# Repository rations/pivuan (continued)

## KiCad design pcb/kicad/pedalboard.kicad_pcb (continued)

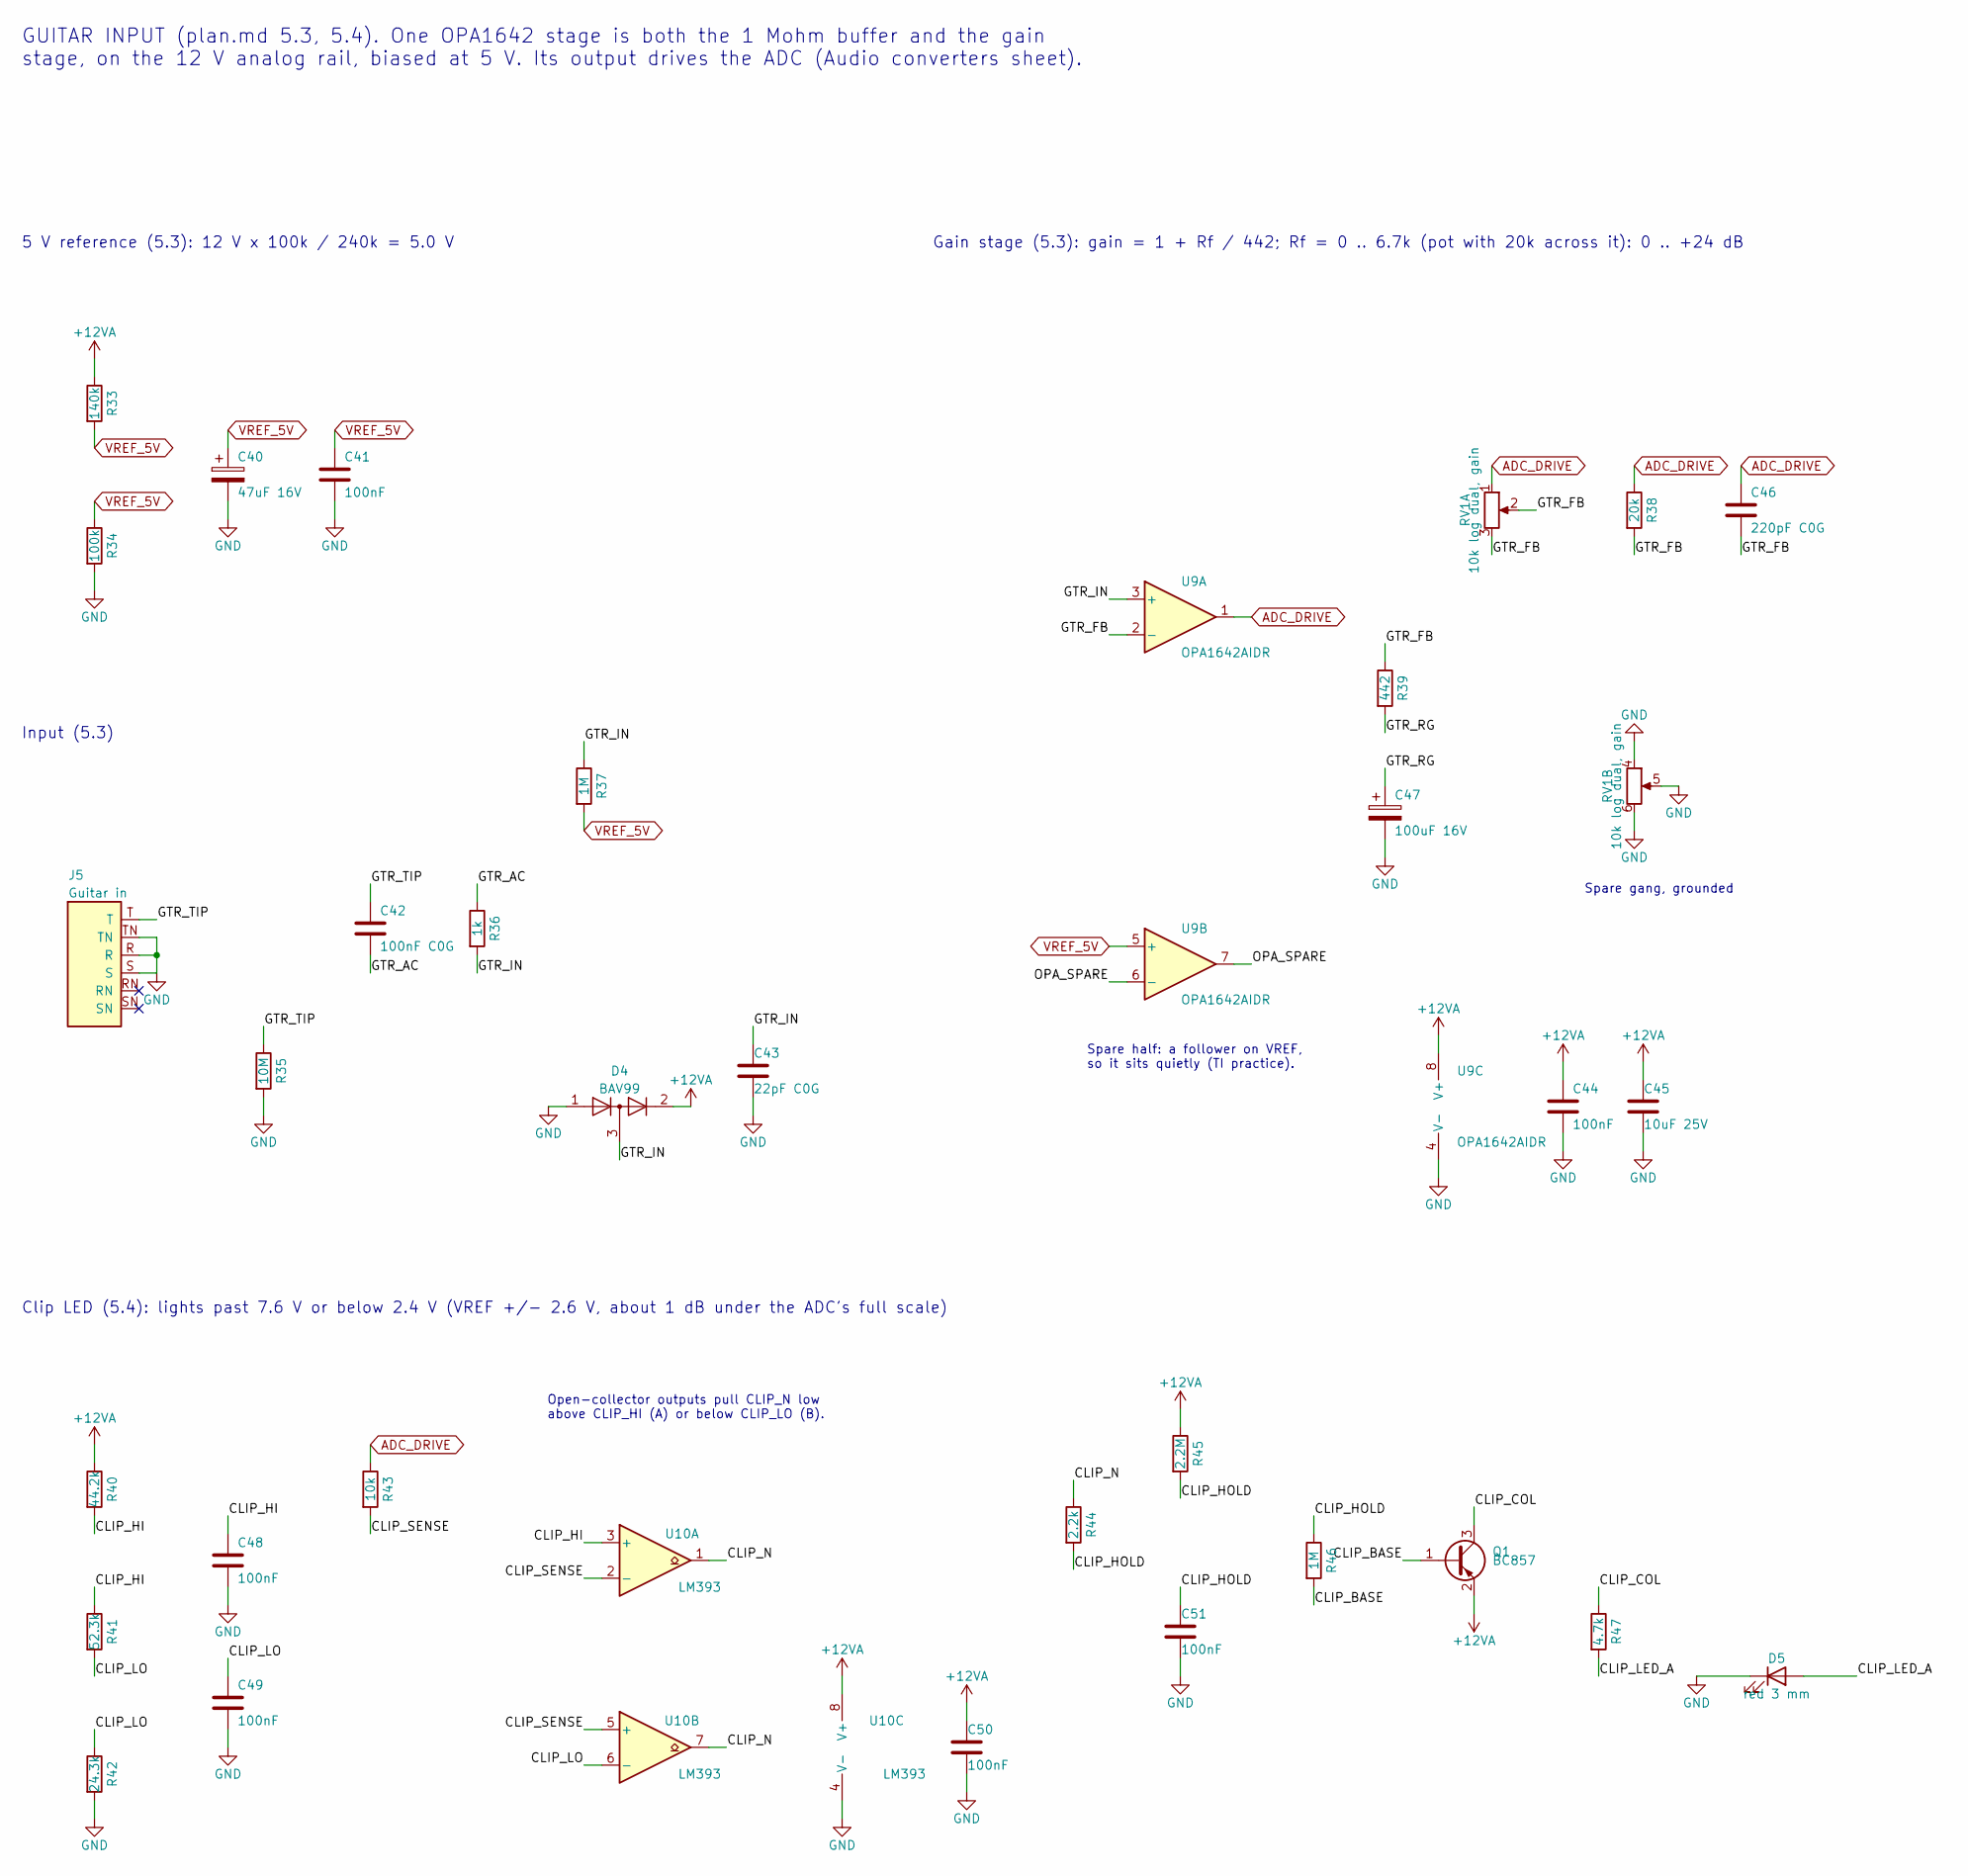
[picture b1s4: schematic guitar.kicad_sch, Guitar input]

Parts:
C40: 47uF 16V; CP_Elec_5x5.4; MPN RVT1C470M0505; LCSC C72515
C41, C44, C48, C49, C50, C51: 100nF; C_0603_1608Metric; MPN CC0603KRX7R9BB104; LCSC C14663
C42: 100nF C0G; C_1206_3216Metric; MPN GRM31C5C1H104JA01L; LCSC C97946
C43: 22pF C0G; C_0603_1608Metric; MPN CL10C220JB8NNNC; LCSC C1653
C45: 10uF 25V; C_1206_3216Metric; MPN CL31A106KBHNNNE; LCSC C13585
C46: 220pF C0G; C_0603_1608Metric; MPN GCM1885C2A221JA16D; LCSC C388907
C47: 100uF 16V; CP_Elec_6.3x5.4; MPN RVT1C101M0605; LCSC C72475
D4: BAV99; SOT-23; MPN BAV99,215; LCSC C2500
D5: red 3 mm; LED_D3.0mm_Horizontal_O1.27mm_Z6.0mm; MPN 204-10SURD/S530-A3-L; LCSC C99771
J5: Guitar in; Jack_6.35mm_Neutrik_NMJ6HCD2_Horizontal; MPN NMJ6HCD2; LCSC C368502
Q1: BC857; SOT-23; MPN BC857C,215; LCSC C8666
R33: 140k; R_0603_1608Metric; MPN RC0603FR-07140KL; LCSC C185372
R34: 100k; R_0603_1608Metric; MPN 0603WAF1003T5E; LCSC C25803
R35: 10M; R_0603_1608Metric; MPN 0603WAF1005T5E; LCSC C7250
R36: 1k; R_0603_1608Metric; MPN 0603WAF1001T5E; LCSC C21190
R37, R46: 1M; R_0603_1608Metric; MPN 0603WAF1004T5E; LCSC C22935
R38: 20k; R_0603_1608Metric; MPN 0603WAF2002T5E; LCSC C4184
R39: 442; R_0603_1608Metric; MPN 0603WAF4420T5E; LCSC C23057
R40: 44.2k; R_0603_1608Metric; MPN AT0603BRD0744K2L; LCSC C855860
R41: 52.3k; R_0603_1608Metric; MPN RS-03K5232FT; LCSC C304764
R42: 24.3k; R_0603_1608Metric; MPN RT0603BRD0724K3L; LCSC C136968
R43: 10k; R_0603_1608Metric; MPN 0603WAF1002T5E; LCSC C25804
R44: 2.2k; R_0603_1608Metric; MPN 0603WAF2201T5E; LCSC C4190
R45: 2.2M; R_0603_1608Metric; MPN 0603WAF2204T5E; LCSC C22938
R47: 4.7k; R_0603_1608Metric; MPN 0603WAF4701T5E; LCSC C23162
RV1: 10k log dual, gain; Potentiometer_Alps_RK09L_Double_Horizontal; MPN RK09L12B0A4S
U9: OPA1642AIDR; SOIC-8_3.9x4.9mm_P1.27mm; MPN OPA1642AIDR; LCSC C67640
U10: LM393; SOIC-8_3.9x4.9mm_P1.27mm; MPN LM393DR2G; LCSC C7955

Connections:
+12VA: C44.1, C45.1, C50.1, D4.2 (A), Q1.2 (E), R33.1, R40.1, R45.1, U9.8 (V+), U10.8 (V+); also elsewhere on the board
/Guitar input/CLIP_BASE: Q1.1 (B), R46.2
/Guitar input/CLIP_COL: Q1.3 (C), R47.1
/Guitar input/CLIP_HI: C48.1, R40.2, R41.1, U10.3 (+)
/Guitar input/CLIP_HOLD: C51.1, R44.2, R45.2, R46.1
/Guitar input/CLIP_LED_A: D5.2 (A), R47.2
/Guitar input/CLIP_LO: C49.1, R41.2, R42.1, U10.6 (-)
/Guitar input/CLIP_N: R44.1, U10.1, U10.7
/Guitar input/CLIP_SENSE: R43.2, U10.2 (-), U10.5 (+)
/Guitar input/GTR_AC: C42.2, R36.1
/Guitar input/GTR_FB: C46.2, R38.2, R39.1, RV1.2, RV1.3, U9.2 (-)
/Guitar input/GTR_IN: C43.1, D4.3 (K), R36.2, R37.1, U9.3 (+)
/Guitar input/GTR_RG: C47.1, R39.2
/Guitar input/GTR_TIP: C42.1, J5.T, R35.1
/Guitar input/OPA_SPARE: U9.6 (-), U9.7
ADC_DRIVE: C46.1, R38.1, R43.1, RV1.1, U9.1; also elsewhere on the board
GND: C40.2, C41.2, C43.2, C44.2, C45.2, C47.2, C48.2, C49.2, C50.2, C51.2, D4.1 (K), D5.1 (K), J5.R, J5.S, J5.TN, R34.2, R35.2, R42.2, RV1.4, RV1.5, RV1.6, U9.4 (V-), U10.4 (V-); also elsewhere on the board
VREF_5V: C40.1, C41.1, R33.2, R34.1, R37.2, U9.5 (+); also elsewhere on the board

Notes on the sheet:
GUITAR INPUT (plan.md 5.3, 5.4). One OPA1642 stage is both the 1 Mohm buffer and the gain stage, on the 12 V analog rail, biased at 5 V. Its output drives the ADC (Audio converters sheet).
5 V reference (5.3): 12 V x 100k / 240k = 5.0 V
Input (5.3)
Gain stage (5.3): gain = 1 + Rf / 442; Rf = 0 .. 6.7k (pot with 20k across it): 0 .. +24 dB
Spare half: a follower on VREF, so it sits quietly (TI practice).
Spare gang, grounded
Clip LED (5.4): lights past 7.6 V or below 2.4 V (VREF +/- 2.6 V, about 1 dB under the ADC's full scale)
Open-collector outputs pull CLIP_N low above CLIP_HI (A) or below CLIP_LO (B).

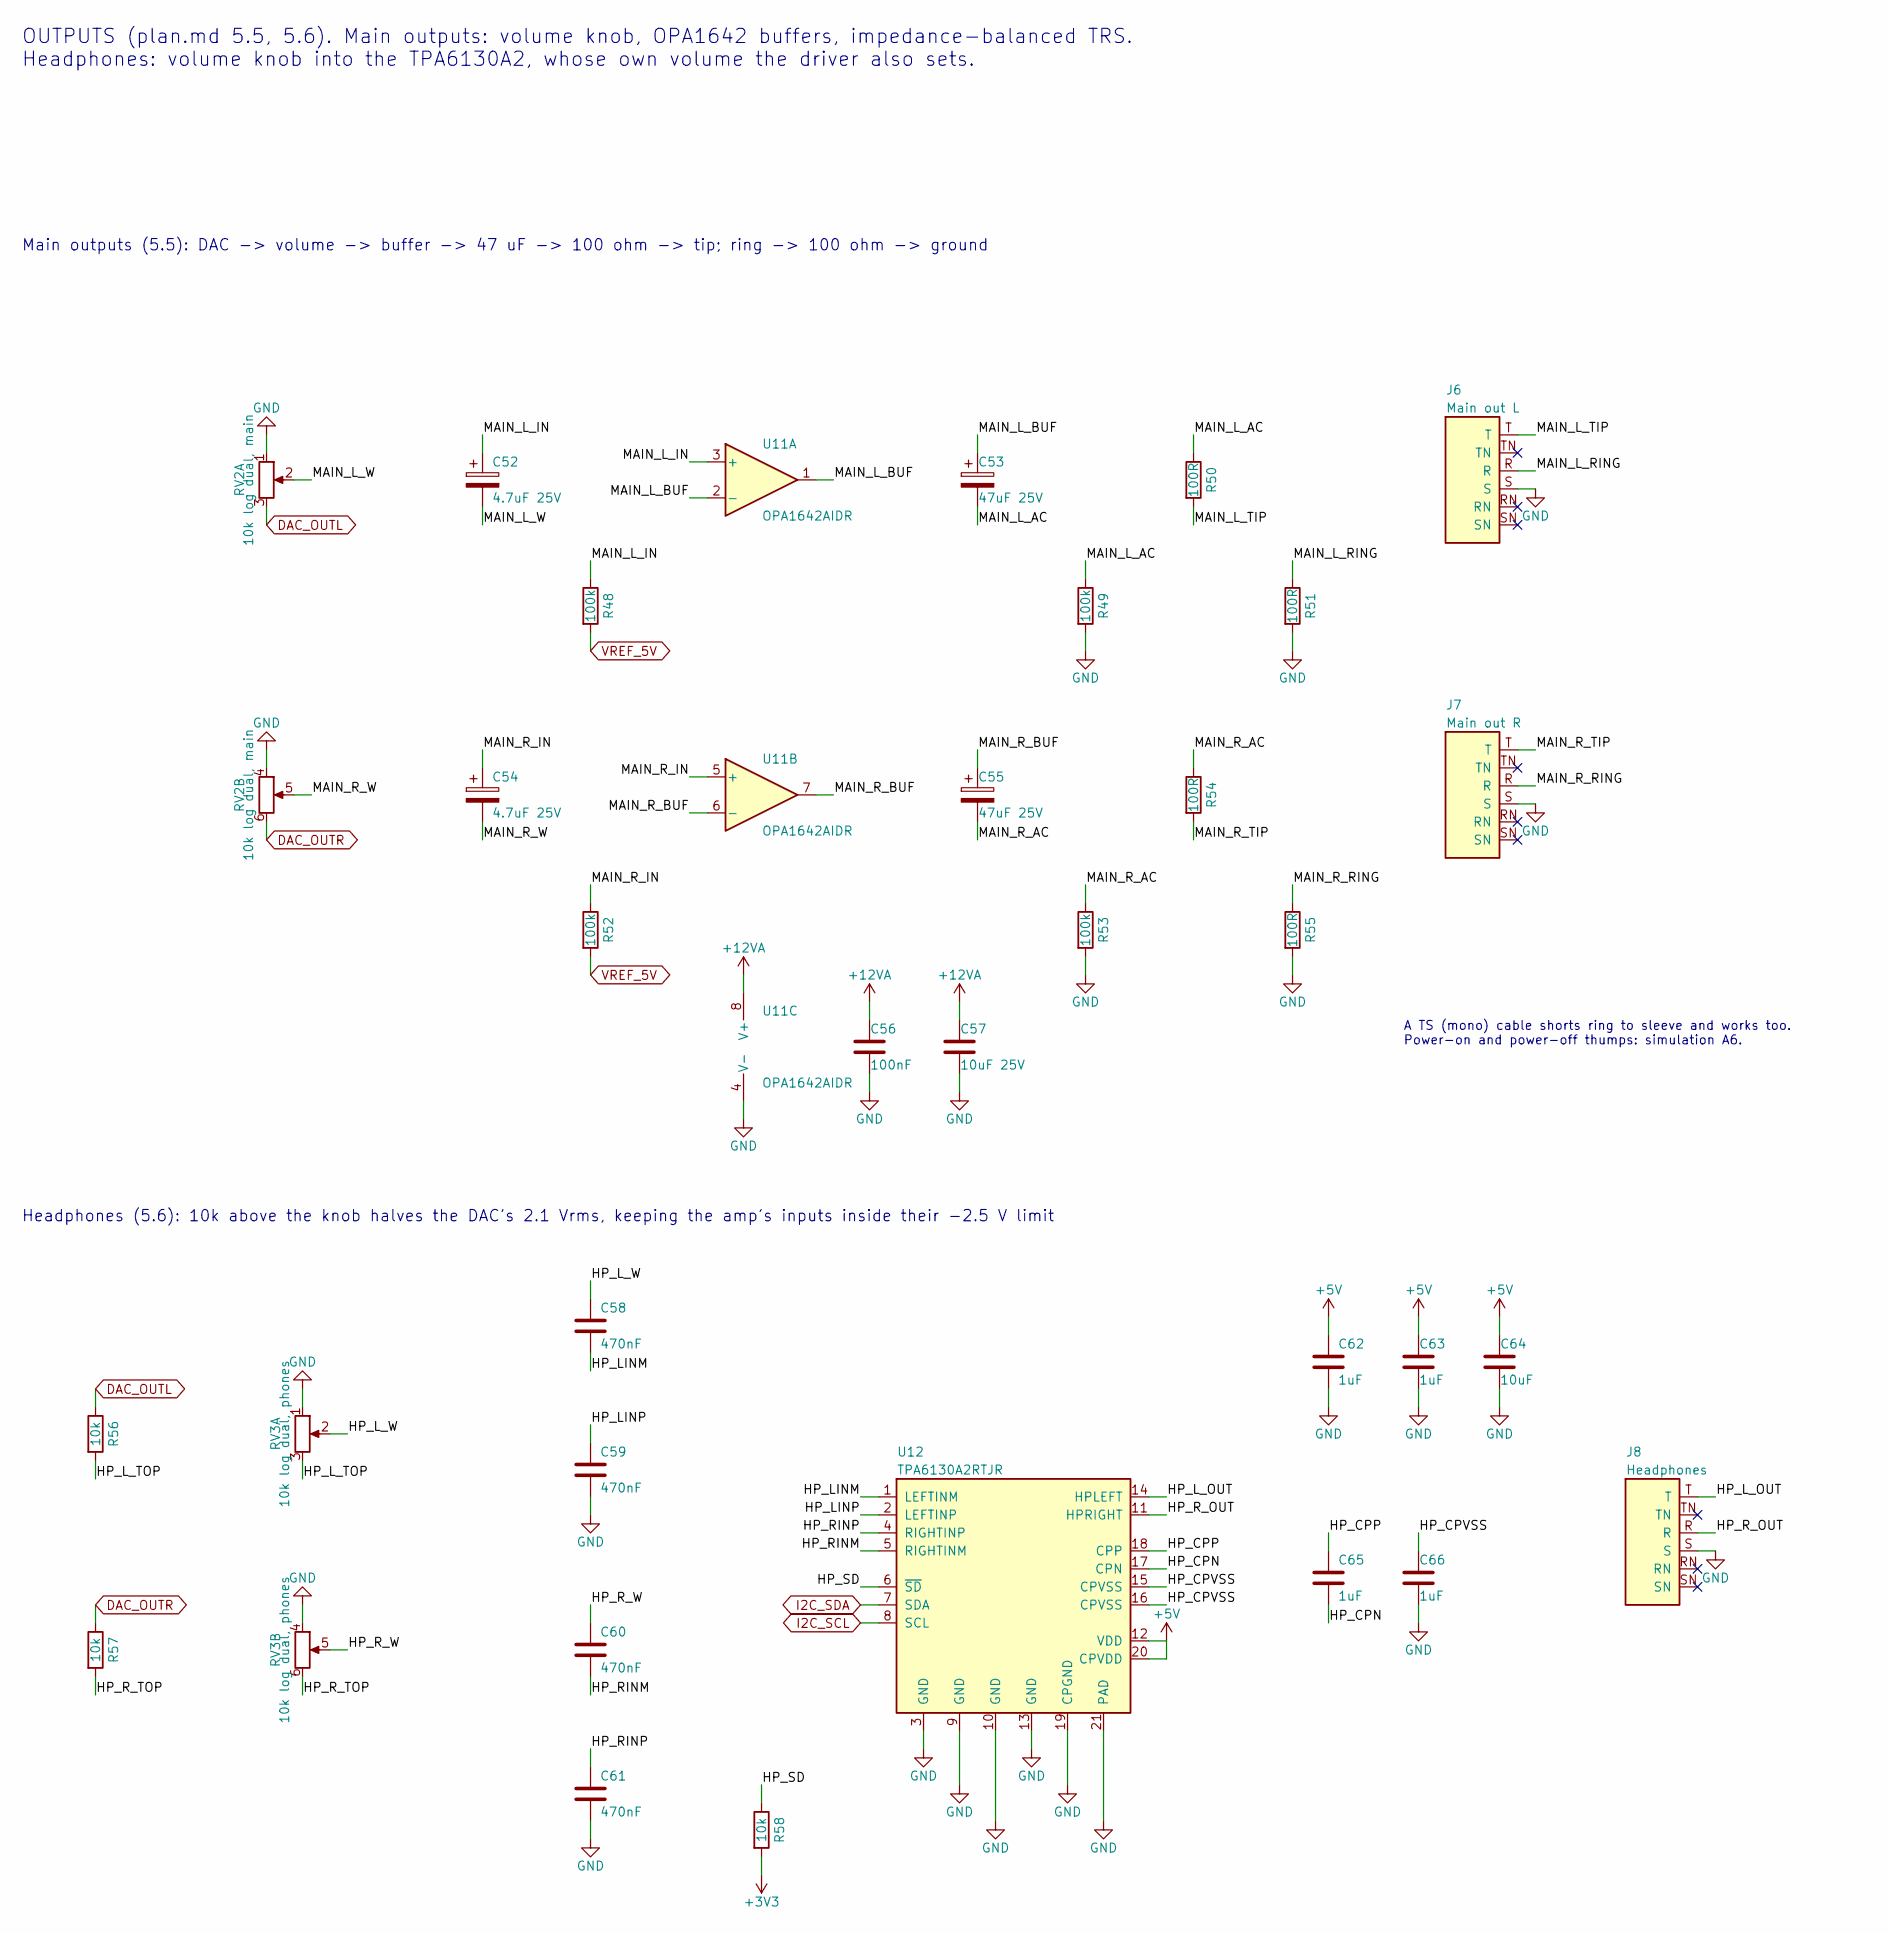
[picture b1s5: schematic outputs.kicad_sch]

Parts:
C52, C54: 4.7uF 25V; CP_Elec_4x5.4; MPN RVT1V4R7M0405; LCSC C72511
C53, C55: 47uF 25V; CP_Elec_6.3x5.4; MPN RVT1E470M0605; LCSC C72521
C56: 100nF; C_0603_1608Metric; MPN CC0603KRX7R9BB104; LCSC C14663
C57: 10uF 25V; C_1206_3216Metric; MPN CL31A106KBHNNNE; LCSC C13585
C58, C59, C60, C61: 470nF; C_0805_2012Metric; MPN CL21B474KBFNNNE; LCSC C13967
C62, C63, C65, C66: 1uF; C_0603_1608Metric; MPN CL10A105KB8NNNC; LCSC C15849
C64: 10uF; C_0805_2012Metric; MPN CL21A106KAYNNNE; LCSC C15850
J6: Main out L; Jack_6.35mm_Neutrik_NMJ6HCD2_Horizontal; MPN NMJ6HCD2; LCSC C368502
J7: Main out R; Jack_6.35mm_Neutrik_NMJ6HCD2_Horizontal; MPN NMJ6HCD2; LCSC C368502
J8: Headphones; Jack_6.35mm_Neutrik_NMJ6HCD2_Horizontal; MPN NMJ6HCD2; LCSC C368502
R48, R49, R52, R53: 100k; R_0603_1608Metric; MPN 0603WAF1003T5E; LCSC C25803
R50, R51, R54, R55: 100R; R_0603_1608Metric; MPN 0603WAF1000T5E; LCSC C22775
R56, R57, R58: 10k; R_0603_1608Metric; MPN 0603WAF1002T5E; LCSC C25804
RV2: 10k log dual, main; Potentiometer_Alps_RK09L_Double_Horizontal; MPN RK09L12B0A4S
RV3: 10k log dual, phones; Potentiometer_Alps_RK09L_Double_Horizontal; MPN RK09L12B0A4S
U11: OPA1642AIDR; SOIC-8_3.9x4.9mm_P1.27mm; MPN OPA1642AIDR; LCSC C67640
U12: TPA6130A2RTJR; QFN-20-1EP_4x4mm_P0.5mm_EP2.7x2.7mm; MPN TPA6130A2RTJR; LCSC C130046

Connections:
+3V3: R58.2; also elsewhere on the board
+5V: C62.1, C63.1, C64.1, U12.12 (VDD), U12.20 (CPVDD); also elsewhere on the board
+12VA: C56.1, C57.1, U11.8 (V+); also elsewhere on the board
/Outputs/HP_CPN: C65.2, U12.17 (CPN)
/Outputs/HP_CPP: C65.1, U12.18 (CPP)
/Outputs/HP_CPVSS: C66.1, U12.15 (CPVSS), U12.16 (CPVSS)
/Outputs/HP_LINM: C58.2, U12.1 (LEFTINM)
/Outputs/HP_LINP: C59.1, U12.2 (LEFTINP)
/Outputs/HP_L_OUT: J8.T, U12.14 (HPLEFT)
/Outputs/HP_L_TOP: R56.2, RV3.3
/Outputs/HP_L_W: C58.1, RV3.2
/Outputs/HP_RINM: C60.2, U12.5 (RIGHTINM)
/Outputs/HP_RINP: C61.1, U12.4 (RIGHTINP)
/Outputs/HP_R_OUT: J8.R, U12.11 (HPRIGHT)
/Outputs/HP_R_TOP: R57.2, RV3.6
/Outputs/HP_R_W: C60.1, RV3.5
/Outputs/HP_SD: R58.1, U12.6 (~SD)
/Outputs/MAIN_L_AC: C53.2, R49.1, R50.1
/Outputs/MAIN_L_BUF: C53.1, U11.1, U11.2 (-)
/Outputs/MAIN_L_IN: C52.1, R48.1, U11.3 (+)
/Outputs/MAIN_L_RING: J6.R, R51.1
/Outputs/MAIN_L_TIP: J6.T, R50.2
/Outputs/MAIN_L_W: C52.2, RV2.2
/Outputs/MAIN_R_AC: C55.2, R53.1, R54.1
/Outputs/MAIN_R_BUF: C55.1, U11.6 (-), U11.7
/Outputs/MAIN_R_IN: C54.1, R52.1, U11.5 (+)
/Outputs/MAIN_R_RING: J7.R, R55.1
/Outputs/MAIN_R_TIP: J7.T, R54.2
/Outputs/MAIN_R_W: C54.2, RV2.5
DAC_OUTL: R56.1, RV2.3; also elsewhere on the board
DAC_OUTR: R57.1, RV2.6; also elsewhere on the board
GND: C56.2, C57.2, C59.2, C61.2, C62.2, C63.2, C64.2, C66.2, J6.S, J7.S, J8.S, R49.2, R51.2, R53.2, R55.2, RV2.1, RV2.4, RV3.1, RV3.4, U11.4 (V-), U12.3 (GND), U12.9 (GND), U12.10 (GND), U12.13 (GND), U12.19 (CPGND), U12.21 (PAD); also elsewhere on the board
I2C_SCL: U12.8 (SCL); also elsewhere on the board
I2C_SDA: U12.7 (SDA); also elsewhere on the board
VREF_5V: R48.2, R52.2; also elsewhere on the board

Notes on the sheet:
OUTPUTS (plan.md 5.5, 5.6). Main outputs: volume knob, OPA1642 buffers, impedance-balanced TRS. Headphones: volume knob into the TPA6130A2, whose own volume the driver also sets.
Main outputs (5.5): DAC -> volume -> buffer -> 47 uF -> 100 ohm -> tip; ring -> 100 ohm -> ground
A TS (mono) cable shorts ring to sleeve and works too. Power-on and power-off thumps: simulation A6.
Headphones (5.6): 10k above the knob halves the DAC's 2.1 Vrms, keeping the amp's inputs inside their -2.5 V limit

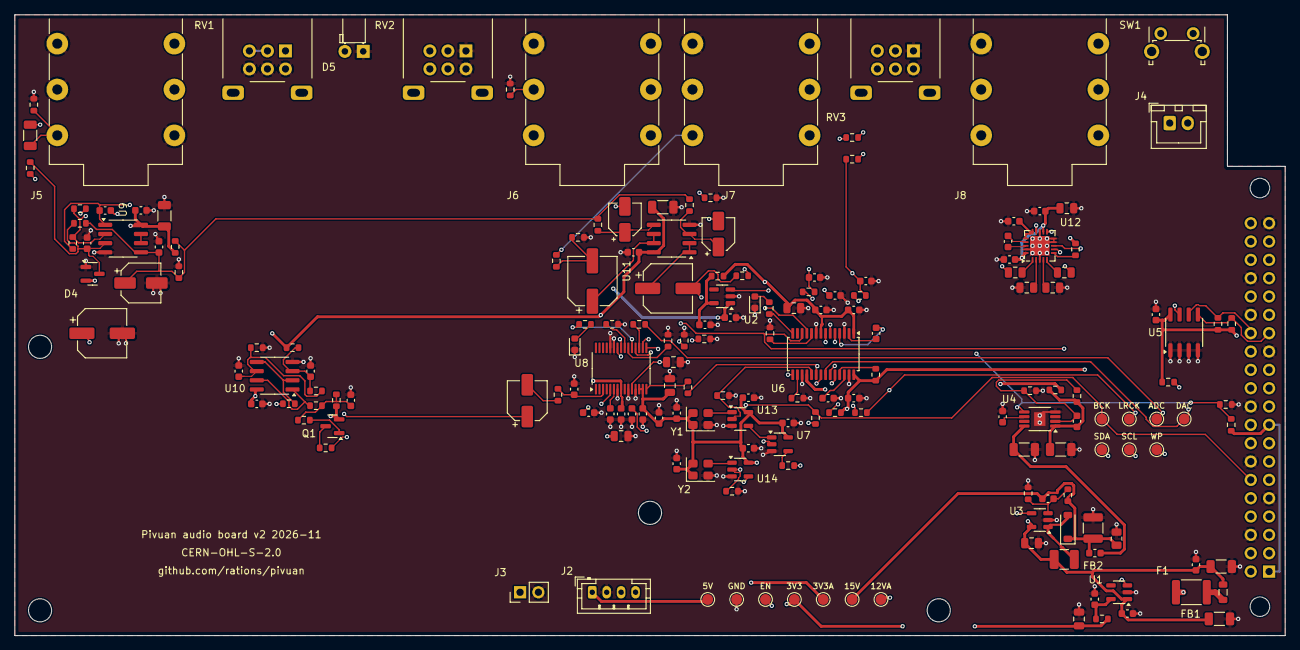
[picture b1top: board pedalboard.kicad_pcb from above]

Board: 4 copper layers, 176.0 x 86.0 mm, 184 parts (1 on the bottom side), 107 nets.

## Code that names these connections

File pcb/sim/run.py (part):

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
    # Response with a pickup and lead, against the same pickup into an ideal 1 Mohm input; and
    # the same with other values of the RF filter capacitor at the op-amp pin.
    rf_cap = [r for r in STAGE if PARTS[r].lib == "Device:C" and set(PARTS[r].pins.values()) == {"GTR_IN", "0"}][0]
    series = []
    for cval in [PARTS[rf_cap].value] + [v for v in ("100pF", "47pF", "22pF", "10pF")
                                          if v != PARTS[rf_cap].value.split()[0]]:
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        lines = kinet.spice(PARTS, ADC_NET) + [f"V_drive ADC_DRIVE 0 {wave}"] + load + ADC_ESD
        ngspice(name, lines, [tran, f"wrdata {name}.dat v(ADC_VINL1) i(V_esd_lo_i) i(V_esd_hi_i)"], models=AUDIO_MODELS)
        d = data(f"{name}.dat")
        pin = d["v(ADC_VINL1)"]
        cur = max(max(abs(x) for x in d["i(V_esd_lo_i)"]), max(abs(x) for x in d["i(V_esd_hi_i)"])) * 1e3
        ok &= check(f"ADC pin, {label}: ESD diode current under 5 mA", cur < 5.0,
                    f"{cur:.2f} mA at most; pin between {min(pin):+.2f} and {max(pin):+.2f} V")
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# --- Outputs: plan 5.5 and 5.6, from the DAC's output pins --------------------------------

OUTPUTS = [r for r in kinet.on_sheet(PARTS, "Outputs") if r != "U12" and not
           set(PARTS[r].pins.values()) & {"P5V", "HP_CPP", "HP_CPN", "HP_CPVSS", "HP_SD"}]
DAC_NET = [r for r in kinet.touching(PARTS, kinet.on_sheet(PARTS, "Audio converters and clocks"),
                                     ["DAC_OUTL_RAW", "DAC_OUTR_RAW"]) if not r.startswith("U")]
# The 5 V reference: the divider and its capacitors (guitar sheet).
VREF_NET = [r for r in GUITAR if set(PARTS[r].pins.values()) <= {"VREF_5V", "P12VA", "0"} and r[0] in "RC"]
# The TPA6130A2 has no SPICE model. Its inputs are each half of its differential input
# impedance, to an internal point at AC ground; 37 kohm is the least, at its highest gains
# (datasheet 9.2.2.1).
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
